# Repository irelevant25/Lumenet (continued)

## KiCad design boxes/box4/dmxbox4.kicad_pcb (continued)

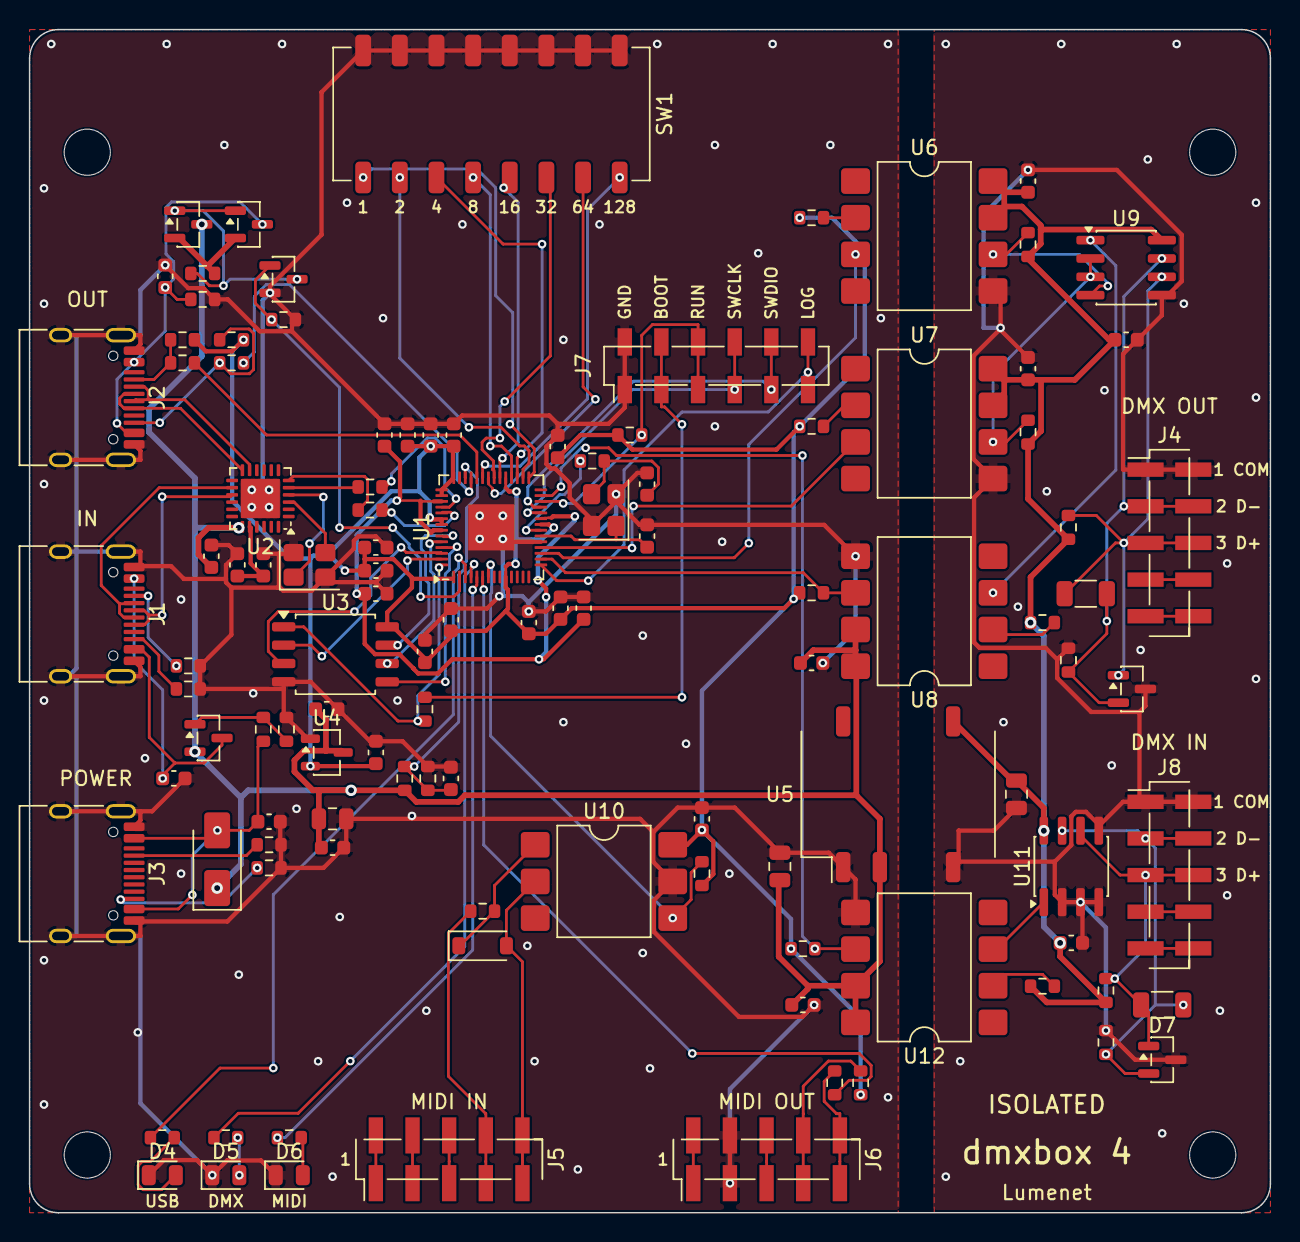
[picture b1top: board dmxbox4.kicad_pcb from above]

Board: 2 copper layers, 86.0 x 82.0 mm, 114 parts (0 on the bottom side), 84 nets.

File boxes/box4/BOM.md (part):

# dmxbox 4: parts and how to order them

dmxbox 4 (box 4) has one DMX output with RDM, one DMX input (a console plays the desk), MIDI IN and OUT, and a
USB hub: boxes can be chained, computer →
first box → second box → … over USB-C cables. Each box is its own USB network adapter on the computer.
Designators (U1, R3, …) match the [schematic](dmxbox4_schematic.pdf) and the [assembly drawing](dmxbox4_assembly.pdf).

The board is 86 × 82 mm, two layers. JLCPCB makes it and solders every part on it, all on the top side. You make
four cables to the sockets in the box wall.

## 1. The board from JLCPCB

Upload [jlcpcb/dmxbox4_gerbers.zip](jlcpcb/dmxbox4_gerbers.zip) on the PCB quote page. The defaults fit:
2 layers, FR-4, 1.6 mm, any color, HASL lead-free, 5 boards. Then switch on **PCB Assembly**:

* Economic, top side, the number of boards to assemble (2 is the minimum).
* BOM: [jlcpcb/dmxbox4_bom.csv](jlcpcb/dmxbox4_bom.csv); placement: [jlcpcb/dmxbox4_cpl.csv](jlcpcb/dmxbox4_cpl.csv).
* Check the placement preview: JLCPCB's pink pin-1 dot of every chip and transistor must sit at the pin-1 mark of
  the silkscreen, the diodes' "−" at their band, the USB sockets' openings at the board edge, J4 to J7 along their
  pads (either end first is fine) and SW1's keys towards the board edge. KiCad and JLCPCB do not agree on every
  part's rotation: the CPL file turns each part the way JLCPCB's preview of 27 November 2026 showed it right.
  Tick **Confirm Parts Placement** and JLCPCB's engineers check it too.

110 parts on 43 lines, all in stock on 28 November 2026. Eleven are extended parts (about $3 each per order):

| Ref | Part | LCSC |
|---|---|---|
| U1 | Raspberry Pi RP2040 | C2040 |
| U2 | WCH CH334F, USB 2.0 hub | C5187527 |
| Y1, Y2 | Abracon ABM8-272-T3, 12 MHz (the crystal Raspberry Pi names for the RP2040) | C20625731 |
| U9, U11 | ST ST485BDR, RS-485 (MAX485 pins, 0.3 mA): DMX OUT, DMX IN | C91197 |
| J1, J2, J3 | HRO TYPE-C-31-M-12, USB-C sockets | C165948 |
| U5 | EVISUN B0505XT-1WR3, isolated 5 V to 5 V, 1 W, 1.5 kV (Mornsun's package and pins) | C19188495 |
| U6, U7, U8, U12 | Lite-On 6N137S-TA1-L, optocoupler: DMX send, direction, receive; DMX IN | C92651 |
| U10 | Everlight H11L1S(TA), optocoupler for MIDI IN (MIDI senders at 3.3 V give too little current for a 6N137) | C78589 |
| J4, J8, J5, J6 | hanxia SMD pin header 1 × 5, 2.54 mm: DMX OUT, DMX IN, MIDI IN, MIDI OUT | C41417362 |
| J7 | hanxia SMD socket strip (female) 1 × 6, 2.54 mm: the service pins | C42380984 |
| SW1 | kangshen DSPV08LSGET, piano DIP switch with 8 keys: the box number | C3293170 |

Everything else is a basic part: W25Q128JVSIQ flash, XC6206 3.3 V regulator, AO3401A and 2N7002 transistors,
SS34, 1N4148W, PSM712 (protection of the DMX lines), LEDs, resistors and capacitors. For 5 boards: about $63 of
parts and $43 of fees, plus the boards and shipping (`scripts/check_parts.py` asks JLCPCB for today's numbers).

## 2. What you buy and fit

| Qty | For | Part | Notes |
|---|---|---|---|
| 1 | DMX OUT | XLR 5-pin **female** panel socket XLR-5G-C | In the back wall. |
| 1 | DMX IN | XLR 5-pin **male** panel socket XLR-5W-C | In the back wall, beside DMX OUT. |
| 2 | MIDI IN, MIDI OUT | REAN NYS325, DIN 5-pin 180° female | In the back wall. |
| 4 | J4, J8, J5, J6 | 5 wires with a 1 × 5 female housing, 2.54 mm (Dupont) | From the pin headers on the board to the sockets. |
| 1 | J7 | jumper wire, male to male | For BOOT and RUN, see [below](#6-the-service-pins-j7). |
| | | the printed case | See [section 4](#4-the-case): about 100 g of PETG. |
| 4 | | M3 heat-set inserts, 5.7 mm long, 4.6 mm wide (for example Ruthex M3 × 5.7) | In the case's four posts. |
| 4 | H1 to H4 | M3 hex standoffs, male-female, 25 mm | Through the board into the inserts; the lid sits on them. |
| 4 | | M3 countersunk screws, 6 mm (ISO 10642) | The lid, into the standoffs. |
| 4 | | M3 screws, 10 mm, and nuts | The two XLRs. |
| 4 | | M3 screws, 8 mm, and nuts | The two DINs. |
| 3 | D4, D5, D6 | round light pipes, 3 mm, 25.4 mm (1 inch) below their head, for a 3.2 mm hole | Pushed into the lid, over the LEDs. |
| 4 | | rubber feet | If you like. |

## 3. Wiring the sockets

Pin n of the header is the socket's pin n on all four (pin 1 is at the "1" on the board):

| Header | Socket | Pin 1 | Pin 2 | Pin 3 | Pin 4 | Pin 5 |
|---|---|---|---|---|---|---|
| J4 | DMX OUT (XLR) | common | Data − | Data + | free | free |
| J8 | DMX IN (XLR, male) | common | Data − | Data + | free | free |
| J5 | MIDI IN (DIN) | free | free (MIDI IN leaves its shield open) | free | current in | current out |
| J6 | MIDI OUT (DIN) | free | shield (ground) | free | current out | current in |

J4 and J8 are on the isolated side: pin 1 is the DMX common, not the box's ground.

## 4. The case

A base and a lid printed in PETG, 123 × 127 × 36 mm closed, wider than the board for the four sockets in a row
(seen from behind: MIDI IN, MIDI OUT, DMX IN, DMX OUT):
[case_print/dmxbox4_base.stl](case_print/dmxbox4_base.stl) and [case_print/dmxbox4_lid.stl](case_print/dmxbox4_lid.stl),
each already turned as it prints (the base standing on its floor, the lid on its top). Pictures:
[from the front](3d/dmxbox4_print_front.png), [from the back](3d/dmxbox4_print_back.png),
[opened](3d/dmxbox4_print_open.png). `scripts/make_print_case.py` makes them from the board's layout;
`case_print/dmxbox4_case_print.step` has both parts for changes in a CAD program.

Printing (Bambu Lab P1S, 0.4 mm nozzle, Bambu Studio):

* Filament: your PETG profile. Plate: textured PEI; on a smooth one, glue stick first (PETG holds too hard).
* Layer height 0.2 mm, 5 walls, 5 top and 5 bottom layers, 20 % gyroid infill. No supports and no brim: the
  round holes in the back wall have a flat top that bridges, under the sockets' flanges.
* The labels are 0.6 mm deep. For them in a second color (AMS): load `dmxbox4_base.stl` together with
  `dmxbox4_base_text.stl`, answer "Yes" to loading them as one object of several parts, and give the text part
  the other filament. The same for the lid.

The holes come out a little small when printed; they are drawn 0.1 to 0.3 mm larger. If a socket or a light
pipe is still tight, a drill or a small file by hand is enough.

The case does not conduct, so the DMX side's isolation cannot be bridged through it, and any screws will do.

The aluminium case of [section 7](#7-the-aluminium-case-instead) is the other way, with the same board.

## 5. Putting it together

1. Press the four heat-set inserts into the posts of the base: a soldering iron at about 240 °C, straight down
   until each one is flush, then let it cool.
2. Solder the four cables to the XLR and DIN sockets (pin n to pin n) and screw the sockets into the back wall,
   the nuts inside.
3. Set the board on the posts, SW1 towards the slot in the side and the USB-C sockets in the front openings.
   Screw the four standoffs through its holes into the inserts. Plug the cables onto J4, J8, J5 and J6.
4. Push the three light pipes into the lid from above, put the lid on (its lip goes inside the walls) and screw
   it to the standoffs.
5. Set the box number with SW1, through the slot with a pen tip: a key pressed down adds the number printed
   next to it (1, 2, 4 … 128; go by these, not by any numbers on the switch itself). With the number n the box
   has the address 10.1.n.1 and Art-Net universe n; every box on one computer needs its own number.
6. Plug IN into a computer. A new box has an empty flash, so the RP2040 starts its USB boot loader and a drive
   called RPI-RP2 appears. Run `firmware\build.cmd` once (see DEV.md), then `firmware\flash.cmd`: it copies the
   firmware onto it. Later updates go the same way; flash.cmd then asks the box to restart into its boot loader
   by itself.

## 6. The service pins (J7)

Normally nothing is plugged in here (the case has to come apart for it). The names are on the board, above
the pins:

| Pin | Name | What it is for |
|---|---|---|
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
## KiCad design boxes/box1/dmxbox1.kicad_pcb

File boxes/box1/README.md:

# Box 1: dmxbox 1, the box with the Pico

A Raspberry Pi Pico in socket strips, one DMX output with RDM and the box-number switch; the Pico's micro-USB is
the box's USB socket. Every part is through-hole: JLCPCB makes the bare board and you solder it. Not built yet.

| File or folder | What |
|---|---|
| [BOM.md](BOM.md) | What to order and buy, soldering, the case and putting the box together |
| `jlcpcb/` | The Gerber ZIP for JLCPCB (the board only) |
| `dmxbox1_schematic.pdf`, `dmxbox1_assembly.pdf`, `dmxbox1_copper.pdf` | The drawings |
| `case_print/` | The case printed in PETG: STL files for the slicer |
| `3d/` | The Blender model and the pictures |
| `firmware/` | `box.h` and `dmxbox1.h` make the shared RP2040 firmware box 1's; `build.cmd` builds `dmxbox1.uf2`, `flash.cmd` puts it onto a box |
| `dmxbox1.kicad_*`, `dmxbox1.pretty/` | The KiCad project, made by the scripts |
| `scripts/` | Make the board, the drawings, the pictures and the case from `circuit.py`, with the scripts all boxes share (`boxes/scripts`) |
| [perfboard/](perfboard/README.md) | The first box 1, built on a perfboard (2026-11-19): it only sends, has no switch and answers at 192.168.7.1; its firmware is in `firmware/archive/pico` |

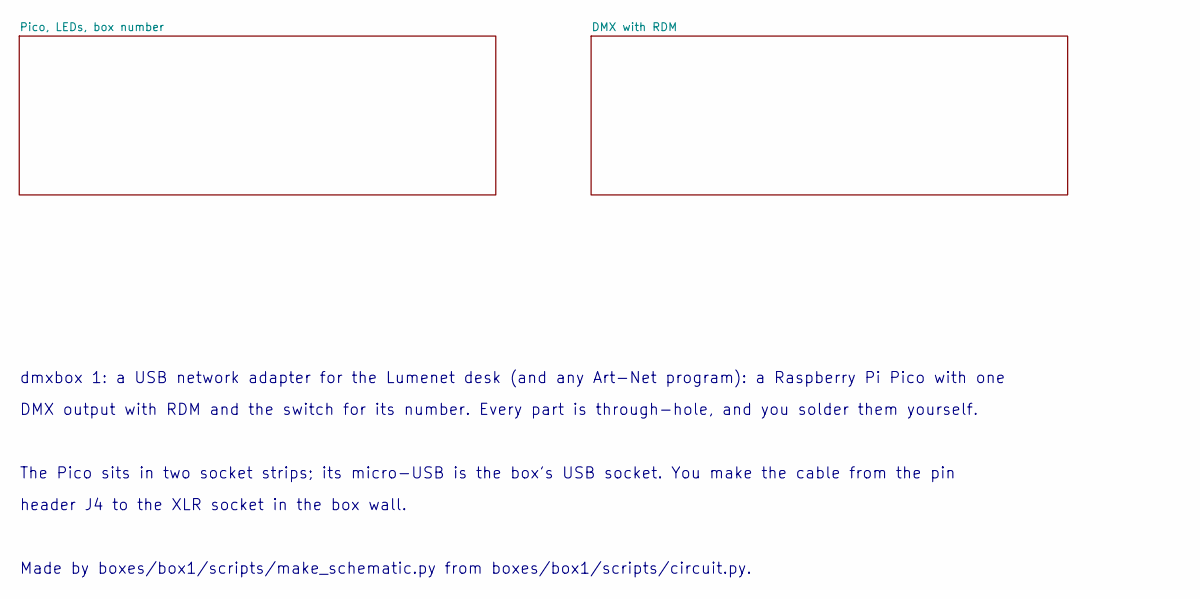
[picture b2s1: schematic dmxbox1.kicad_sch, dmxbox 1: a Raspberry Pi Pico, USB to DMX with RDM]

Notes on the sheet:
dmxbox 1: a USB network adapter for the Lumenet desk (and any Art-Net program): a Raspberry Pi Pico with one
DMX output with RDM and the switch for its number. Every part is through-hole, and you solder them yourself.
The Pico sits in two socket strips; its micro-USB is the box's USB socket. You make the cable from the pin
header J4 to the XLR socket in the box wall.
Made by boxes/box1/scripts/make_schematic.py from boxes/box1/scripts/circuit.py.

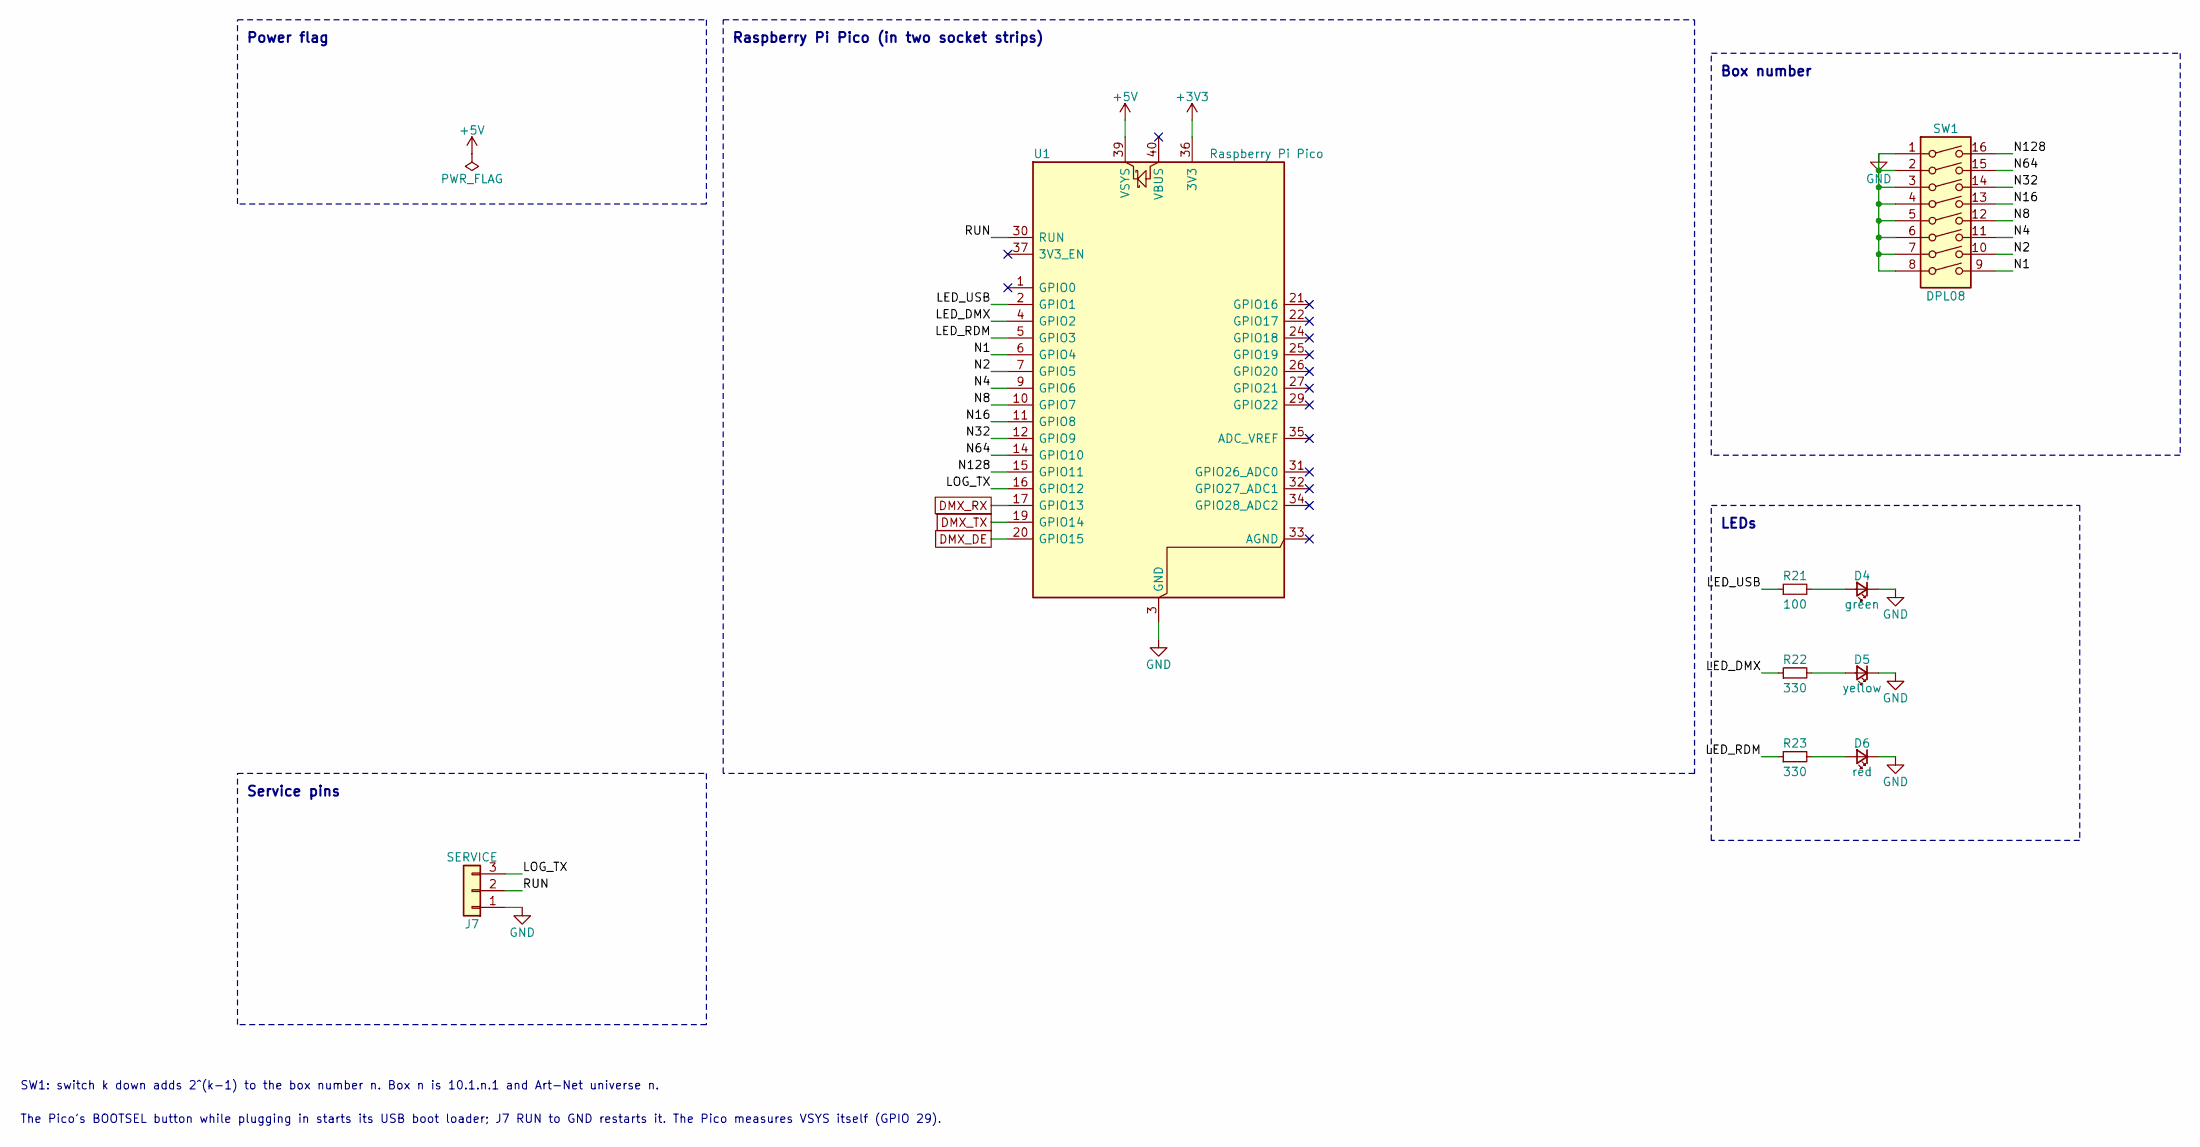
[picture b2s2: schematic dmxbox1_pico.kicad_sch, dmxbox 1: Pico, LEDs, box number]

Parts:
D4: green; LED_D3.0mm
D5: yellow; LED_D3.0mm
D6: red; LED_D3.0mm
J7: SERVICE; PinHeader_1x03_P2.54mm_Vertical
R21: 100; R_Axial_DIN0207_L6.3mm_D2.5mm_P7.62mm_Horizontal
R22, R23: 330; R_Axial_DIN0207_L6.3mm_D2.5mm_P7.62mm_Horizontal
SW1: DPL08; SW_DIP_SPSTx08_Piano_10.8x21.88mm_W7.62mm_P2.54mm
U1: Raspberry Pi Pico; RaspberryPi_Pico_Common_THT

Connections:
+3V3: U1.36 (3V3); also elsewhere on the board
+5V: U1.39 (VSYS); also elsewhere on the board
/Pico, LEDs, box number/LED_DMX: R22.1, U1.4 (GPIO2)
/Pico, LEDs, box number/LED_RDM: R23.1, U1.5 (GPIO3)
/Pico, LEDs, box number/LED_USB: R21.1, U1.2 (GPIO1)
/Pico, LEDs, box number/LOG_TX: J7.3, U1.16 (GPIO12)
/Pico, LEDs, box number/N1: SW1.9, U1.6 (GPIO4)
/Pico, LEDs, box number/N2: SW1.10, U1.7 (GPIO5)
/Pico, LEDs, box number/N4: SW1.11, U1.9 (GPIO6)
/Pico, LEDs, box number/N8: SW1.12, U1.10 (GPIO7)
/Pico, LEDs, box number/N16: SW1.13, U1.11 (GPIO8)
/Pico, LEDs, box number/N32: SW1.14, U1.12 (GPIO9)
/Pico, LEDs, box number/N64: SW1.15, U1.14 (GPIO10)
/Pico, LEDs, box number/N128: SW1.16, U1.15 (GPIO11)
/Pico, LEDs, box number/RUN: J7.2, U1.30 (RUN)
DMX_DE: U1.20 (GPIO15); also elsewhere on the board
DMX_RX: U1.17 (GPIO13); also elsewhere on the board
DMX_TX: U1.19 (GPIO14); also elsewhere on the board
GND: D4.1 (K), D5.1 (K), D6.1 (K), J7.1, SW1.1, SW1.2, SW1.3, SW1.4, SW1.5, SW1.6, SW1.7, SW1.8, U1.3 (GND), U1.8 (GND), U1.13 (GND), U1.18 (GND), U1.23 (GND), U1.28 (GND), U1.38 (GND); also elsewhere on the board
unnamed: D4.2 (A), R21.2
unnamed: D5.2 (A), R22.2
unnamed: D6.2 (A), R23.2

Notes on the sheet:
Raspberry Pi Pico (in two socket strips)
Power flag
Service pins
LEDs
Box number
SW1: switch k down adds 2^(k-1) to the box number n. Box n is 10.1.n.1 and Art-Net universe n.
The Pico's BOOTSEL button while plugging in starts its USB boot loader; J7 RUN to GND restarts it. The Pico measures VSYS itself (GPIO 29).

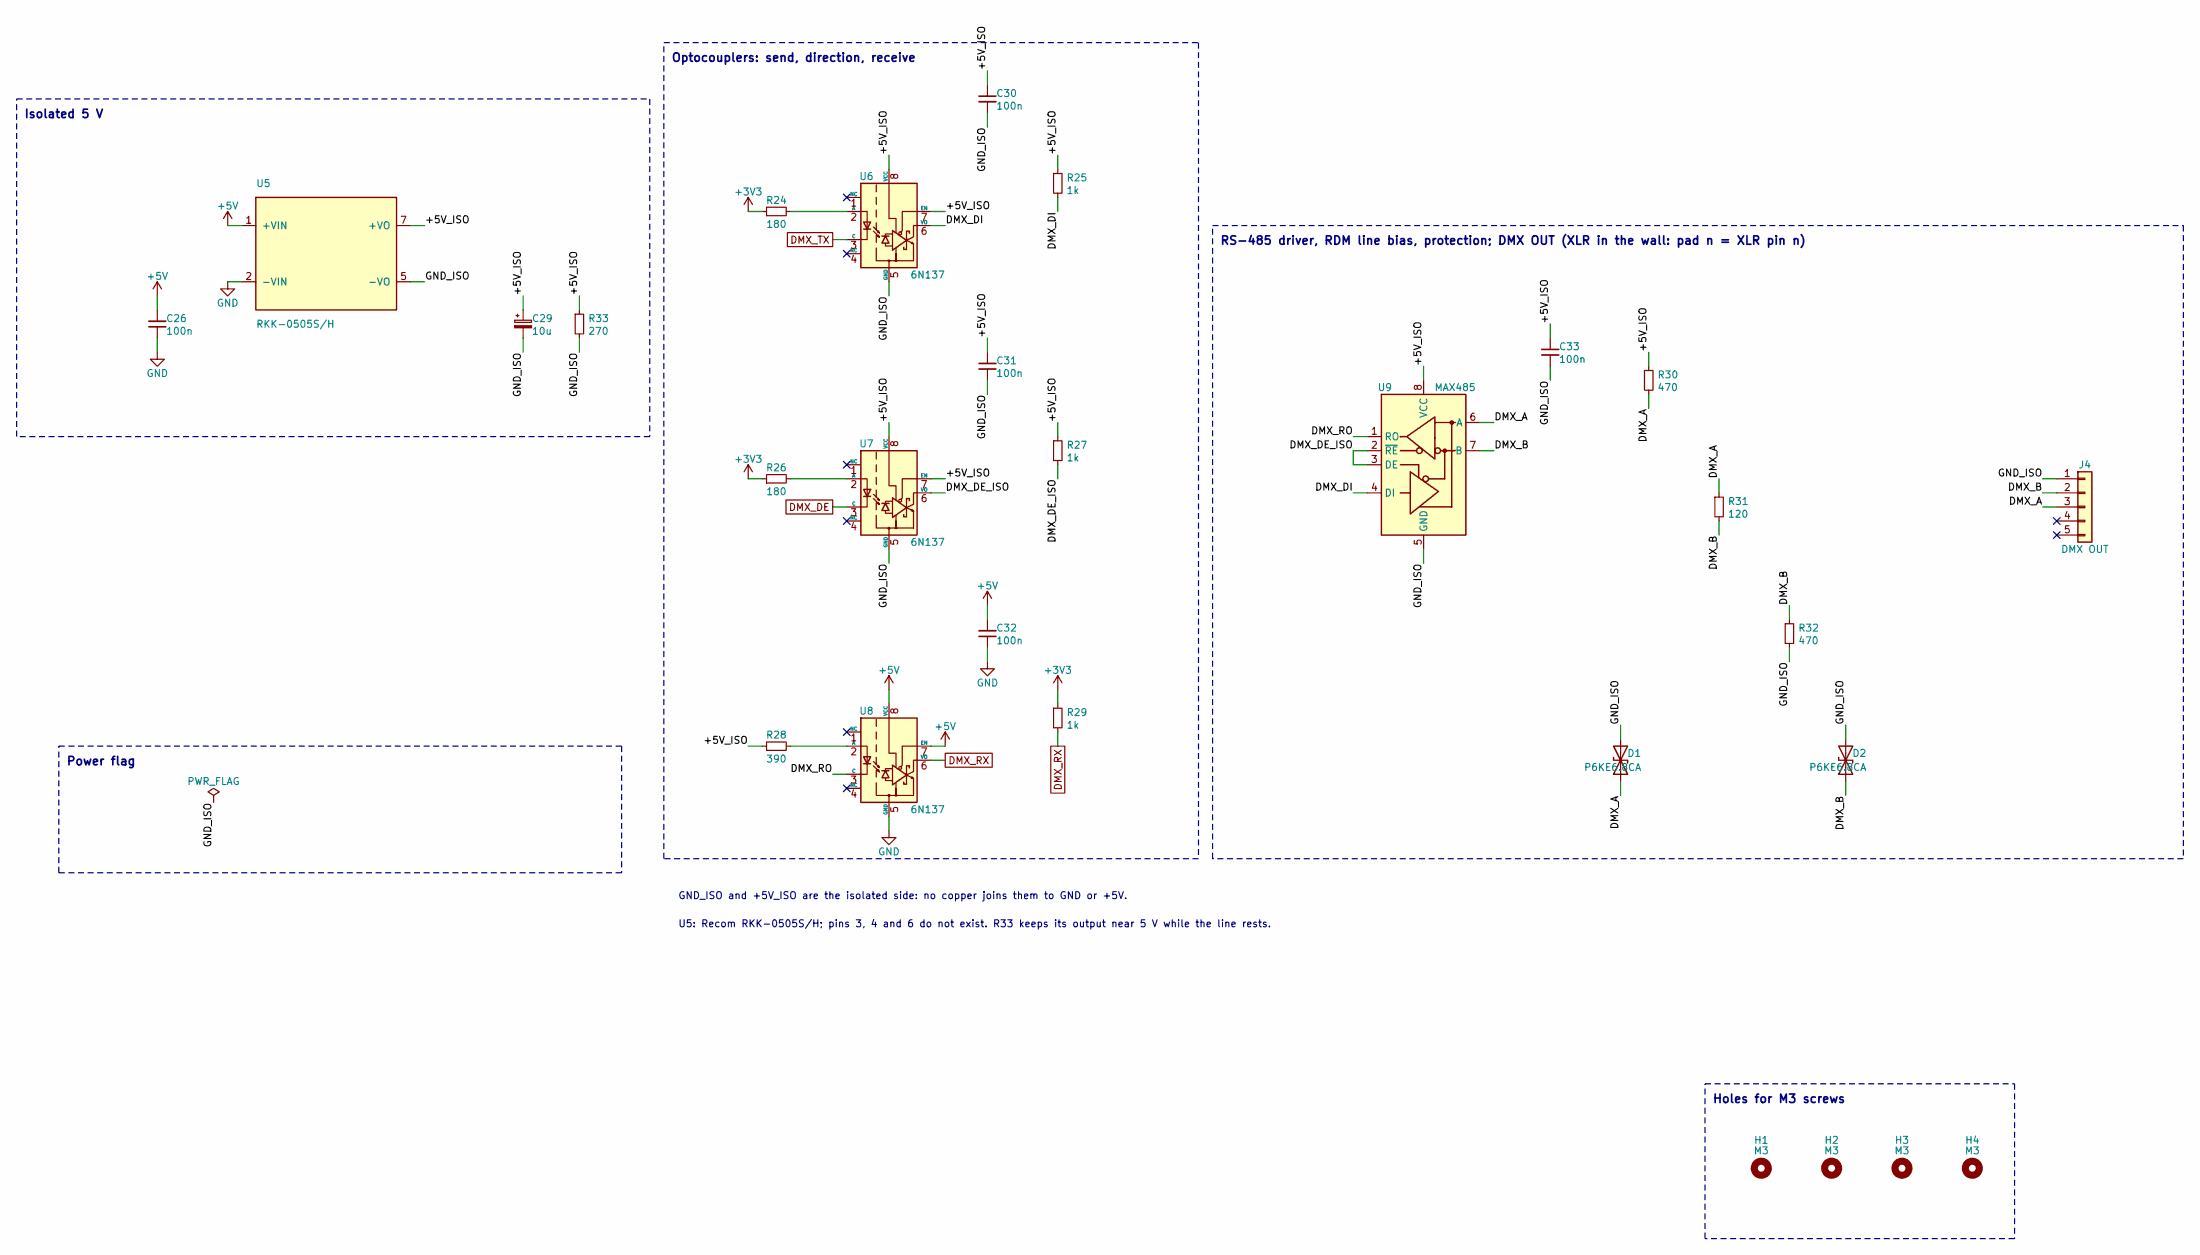
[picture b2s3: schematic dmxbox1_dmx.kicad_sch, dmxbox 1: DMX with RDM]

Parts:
C26, C30, C31, C32, C33: 100n; C_Disc_D5.0mm_W2.5mm_P5.00mm
C29: 10u; CP_Radial_D5.0mm_P2.00mm
D1, D2: P6KE6.8CA; D_DO-15_P10.16mm_Horizontal
H1, H2, H3, H4: M3; MountingHole_3.2mm_M3
J4: DMX OUT; PinHeader_1x05_P2.54mm_Vertical
R24, R26: 180; R_Axial_DIN0207_L6.3mm_D2.5mm_P7.62mm_Horizontal
R25, R27, R29: 1k; R_Axial_DIN0207_L6.3mm_D2.5mm_P7.62mm_Horizontal
R28: 390; R_Axial_DIN0207_L6.3mm_D2.5mm_P7.62mm_Horizontal
R30, R32: 470; R_Axial_DIN0207_L6.3mm_D2.5mm_P7.62mm_Horizontal
R31: 120; R_Axial_DIN0207_L6.3mm_D2.5mm_P7.62mm_Horizontal
R33: 270; R_Axial_DIN0207_L6.3mm_D2.5mm_P7.62mm_Horizontal
U5: RKK-0505S/H; Converter_DCDC_RECOM_RKK_SIP7
U6, U7, U8: 6N137; DIP-8_W7.62mm_Socket
U9: MAX485; DIP-8_W7.62mm_Socket

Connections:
+3V3: R24.1, R26.1, R29.1; also elsewhere on the board
+5V: C26.1, C32.1, U5.1 (+VIN), U8.7 (EN), U8.8 (VCC); also elsewhere on the board
/DMX with RDM/+5V_ISO: C29.1, C30.1, C31.1, C33.1, R25.1, R27.1, R28.1, R30.1, R33.1, U5.7 (+VO), U6.7 (EN), U6.8 (VCC), U7.7 (EN), U7.8 (VCC), U9.8 (VCC)
/DMX with RDM/DMX_A: D1.1 (A1), J4.3, R30.2, R31.1, U9.6 (A)
/DMX with RDM/DMX_B: D2.1 (A1), J4.2, R31.2, R32.1, U9.7 (B)
/DMX with RDM/DMX_DE_ISO: R27.2, U7.6 (VO), U9.2 (~RE), U9.3 (DE)
/DMX with RDM/DMX_DI: R25.2, U6.6 (VO), U9.4 (DI)
/DMX with RDM/DMX_RO: U8.3 (C), U9.1 (RO)
/DMX with RDM/GND_ISO: C29.2, C30.2, C31.2, C33.2, D1.2 (A2), D2.2 (A2), J4.1, R32.2, R33.2, U5.5 (-VO), U6.5 (GND), U7.5 (GND), U9.5 (GND)
DMX_DE: U7.3 (C); also elsewhere on the board
DMX_RX: R29.2, U8.6 (VO); also elsewhere on the board
DMX_TX: U6.3 (C); also elsewhere on the board
GND: C26.2, C32.2, U5.2 (-VIN), U8.5 (GND); also elsewhere on the board
unnamed: R24.2, U6.2 (A)
unnamed: R26.2, U7.2 (A)
unnamed: R28.2, U8.2 (A)

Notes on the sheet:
Isolated 5 V
Optocouplers: send, direction, receive
RS-485 driver, RDM line bias, protection; DMX OUT (XLR in the wall: pad n = XLR pin n)
Holes for M3 screws
Power flag
GND_ISO and +5V_ISO are the isolated side: no copper joins them to GND or +5V.
U5: Recom RKK-0505S/H; pins 3, 4 and 6 do not exist. R33 keeps its output near 5 V while the line rests.

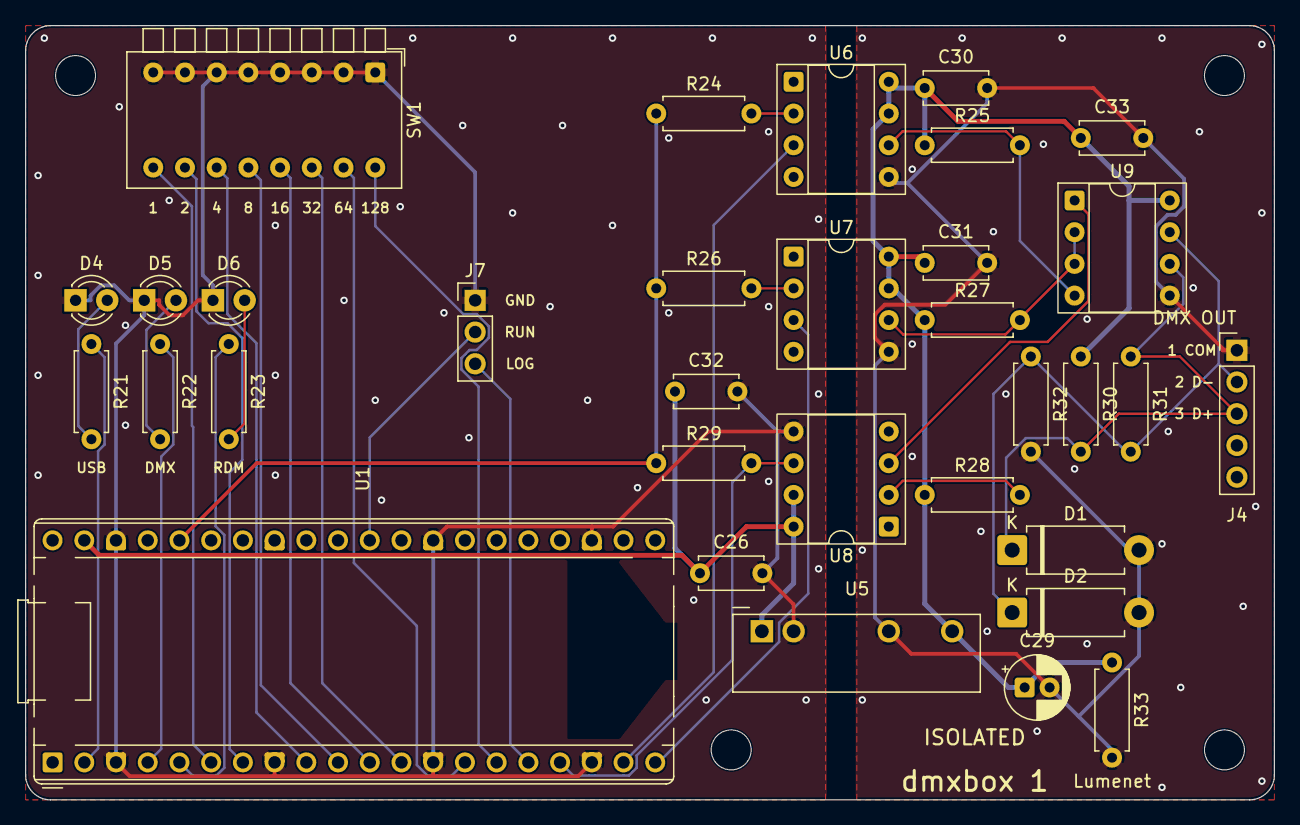
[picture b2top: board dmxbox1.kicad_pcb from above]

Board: 2 copper layers, 100.0 x 62.0 mm, 37 parts (0 on the bottom side), 32 nets.

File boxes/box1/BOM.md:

# dmxbox 1: parts and how to build it

dmxbox 1 (box 1) is a Raspberry Pi Pico with one DMX output with RDM and the switch for its number. The Pico's own
micro-USB is the box's USB socket. Every part is through-hole: JLCPCB makes the bare board and you solder the parts.
Designators (U1, R24, …) match the [schematic](dmxbox1_schematic.pdf) and the
[assembly drawing](dmxbox1_assembly.pdf); the parts that do what box 4's do have box 4's names, so there are gaps.

The board is 100 × 62 mm, two layers.

## 1. The board from JLCPCB

Upload [jlcpcb/dmxbox1_gerbers.zip](jlcpcb/dmxbox1_gerbers.zip) on the PCB quote page. The defaults fit: 2 layers,
FR-4, 1.6 mm, any color, HASL lead-free, 5 boards. No assembly: you solder the parts.

## 2. What you buy

| Qty | Ref | Part | Notes |
|---|---|---|---|
| 1 | U1 | Raspberry Pi Pico | The plain Pico, or the Pico H (its headers already on). |
| 2 | U1 | pin header, male, 1 × 20, 2.54 mm | Only for a plain Pico: solder them to it, pins down. |
| 2 | U1 | socket strip, female, 1 × 20, 2.54 mm, 8.5 mm high | On the board; the Pico plugs in. |
| 3 | U6, U7, U8 | 6N137, optocoupler, DIP-8 | |
| 1 | U9 | MAX485 or SN75176BP, RS-485, DIP-8 | The same pins. |
| 4 | U6 to U9 | IC socket DIP-8, 7.62 mm | |
| 1 | U5 | Recom RKK-0505S/H, isolated DC-DC 5 V to 5 V, 1 W | SIP7 with 4 pins: it fits one way only. |
| 1 | SW1 | piano DIP switch, 8 keys, through-hole, rows 7.62 mm apart (for example ONPOW DPL08RGT) | The keys at the board edge. |
| 1 each | D4, D5, D6 | LED 3 mm: green, yellow, red | |
| 2 | D1, D2 | P6KE6.8CA, TVS diode, DO-15 | "CA": both ways, so either way round. |
| 1 | R21 | 100 Ω | Resistors: 0.25 W, axial (0207), legs bent to 7.62 mm. |
| 2 | R22, R23 | 330 Ω | |
| 2 | R24, R26 | 180 Ω | |
| 3 | R25, R27, R29 | 1 kΩ | |
| 1 | R28 | 390 Ω | |
| 2 | R30, R32 | 470 Ω | |
| 1 | R31 | 120 Ω | |
| 1 | R33 | 270 Ω | |
| 5 | C26, C30 to C33 | 100 nF, ceramic, 5 mm lead spacing | |
| 1 | C29 | 10 µF, electrolytic, 16 V or more, 5 mm wide, 2 mm lead spacing | Mind its "−" stripe. |
| 1 | J4 | pin header, male, 1 × 5, 2.54 mm | To the XLR socket. |
| 1 | J7 | pin header, male, 1 × 3, 2.54 mm | The service pins: GND, RUN, LOG. |
| 1 | DMX OUT | XLR 5-pin **female** panel socket XLR-5G-C | In the back wall. |
| 1 | J4 | 5 wires with a 1 × 5 female housing, 2.54 mm (Dupont) | From J4 to the XLR socket. |
| | | the printed case | See [section 4](#4-the-case): about 70 g of PETG. |
| 4 | | M3 heat-set inserts, 5.7 mm long, 4.6 mm wide (for example Ruthex M3 × 5.7) | In the case's four posts. |
| 4 | H1 to H4 | M3 hex standoffs, male-female, 25 mm | Through the board into the inserts; the lid sits on them. |
| 4 | | M3 countersunk screws, 6 mm (ISO 10642) | The lid, into the standoffs. |
| 2 | | M3 screws, 10 mm, and nuts | The XLR. |
| 3 | D4, D5, D6 | round light pipes, 3 mm, about 19 mm below their head, for a 3.2 mm hole | The LEDs stand 8.3 mm high: a 25.4 mm pipe cut to 19 mm. |
| 4 | | rubber feet | If you like. |
| 1 | | micro-USB cable, for data (not charge-only) | |

## 3. Soldering

Low parts first, so the board lies flat while you solder: the resistors, the diodes D1 and D2, the ceramic
capacitors, the four IC sockets (their notch as on the board), the two socket strips of the Pico, J7 and J4, the
LEDs (the flat side of the rim, the cathode, as on the board; their tops about 8 mm above the board, where the
light pipes end), SW1 (its keys at the board edge), U5 (its pin 1 at the square pad) and C29 (its stripe away from the "+" on the board). Then the chips
into their sockets: the three 6N137 and the MAX485, each with its notch to the notch of the socket.

Test before the chips go in: with the Pico in its sockets and USB plugged in, about 5 V between U5's pins 7 and 5
(the isolated side: 4.6 to 5.5 V).

Wiring the XLR socket: pin n of J4 is the socket's pin n (pin 1 is "1 COM" on the board): 1 common, 2 Data −,
3 Data +, 4 and 5 free. J4 is on the isolated side: pin 1 is the DMX common, not the box's ground.

## 4. The case

A base and a lid printed in PETG, 70 × 141 × 36 mm closed: box 4's case made for this board, with the Pico's
micro-USB in the front wall and the XLR in the middle of the back wall.
[case_print/dmxbox1_base.stl](case_print/dmxbox1_base.stl) and [case_print/dmxbox1_lid.stl](case_print/dmxbox1_lid.stl),
each already turned as it prints. Pictures: [from the front](3d/dmxbox1_print_front.png),
[from the back](3d/dmxbox1_print_back.png), [opened](3d/dmxbox1_print_open.png). Print it as box 4's case
([box 4's BOM.md](../box4/BOM.md#4-the-case)).

## 5. Putting it together

1. Press the four heat-set inserts into the posts of the base: a soldering iron at about 240 °C, straight down
   until each one is flush, then let it cool.
2. Solder the cable to the XLR socket (pin n to pin n) and screw the socket into the back wall, the nuts inside.
3. Set the board on the posts, SW1 towards the slot in the side and the Pico's micro-USB in the front opening.
   Screw the four standoffs through its holes into the inserts. Plug the cable onto J4.
4. Push the three light pipes into the lid from above, put the lid on and screw it to the standoffs.
5. Set the box number with SW1, through the slot with a pen tip: a key pressed down adds the number printed
   next to it (1, 2, 4 … 128 from the left; go by these, not by any numbers on the switch itself). With the
   number n the box has the address 10.1.n.1 and Art-Net universe n; every box on one computer needs its own
   number.
6. Plug it into a computer. A new Pico has an empty flash, so it starts its USB boot loader and a drive called
   RPI-RP2 appears (otherwise hold the Pico's BOOTSEL button while plugging it in). Run `firmware\build.cmd`
   once (see DEV.md), then `firmware\flash.cmd`: it copies the firmware onto it. Later updates go the same way;
   flash.cmd then asks the box to restart into its boot loader by itself.

## 6. The service pins (J7)

| Pin | Name | What it is for |
|---|---|---|
| 1 | GND | ground, for the pins next to it |
| 2 | RUN | joined to GND for a moment: the box restarts |
| 3 | LOG | what the firmware reports, as text: to the RX of a 3.3 V USB-serial adapter (its GND to pin 1), 250000 baud |

The USB boot loader: the Pico's BOOTSEL button while you plug it in.

## Power

The box asks the computer for 250 mA and draws about 150 mA; any USB port gives that.

## The box on its perfboard

The first box 1, on a perfboard, is in [perfboard/](perfboard/README.md): it only sends (no RDM) and has no switch,
answers at 192.168.7.1 and keeps its first firmware (`firmware/archive/pico`); the desk plays it as before.

## Not built yet

This board is the first revision: nothing of it has been built or measured. It passes KiCad's electrical and
design rule checks, and its nets match the schematic.

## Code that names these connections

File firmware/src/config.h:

// dmxbox 3 (RP2040: one DMX output with RDM, MIDI in and out, a USB hub for a
// chain of boxes) - build-time configuration. Everything you are likely to
// change lives here. This file holds numbers only, so the simulator
// (firmware/sim) and the tests (firmware/test) use it too.
#pragma once

#define FW_VERSION_MAJOR 3
#define FW_VERSION_MINOR 0

// ---------------------------------------------------------------- network (inside the USB cable)
// The box shows up on the computer as a USB network adapter and hands the
// computer its address by itself (a tiny DHCP server).
//
// The address comes from the switch SW1 on the board. Its eight switches give
// the box number n, 0 to 255 (switch 1 counts 1, switch 2 counts 2, switch 3
// counts 4 ... switch 8 counts 128; ON counts). The box is 10.1.n.1 and the
// computer gets 10.1.n.2, so every box is a small network of its own, and
// several boxes can be plugged into one computer, also one behind the other.
// Give every box its own number. Lumenet looks for 10.1.n.1 on every network
// adapter of the computer that has an address 10.1.n.x.
//
// If a network you use is in 10.1.x.x, change the first two numbers here.
#define NET_FIRST     10                     // the first two numbers of both addresses
#define NET_SECOND    1
#define NET_NETMASK   {255, 255, 255, 0}
#define NET_LEASE_S   3600                   // the computer asks again after at most this many seconds
// Both Ethernet addresses are made from the box number too: box
// 02:00:0A:01:nn:01, computer 02:00:0A:01:nn:02.

#define ARTNET_PORT    6454   // fixed by the Art-Net spec
#define CTRL_PORT      7000   // our own reliable command protocol
// Art-Net: box n listens to universe ARTNET_UNIVERSE + n.
#define ARTNET_UNIVERSE   0
#define NODE_SHORT_NAME "dmxbox 3"
#define NODE_LONG_NAME  "dmxbox 3 - RP2040 USB Art-Net node with RDM and MIDI"

// In MERGE_ARTNET_OVERRIDE mode, Art-Net is "live" for this long after the
// last packet. After that the box falls back to the cue layer.
#define ARTNET_LIVE_MS 3000

// ---------------------------------------------------------------- USB identity
// 0x1209 / 0x0001 is the "for testing only" number pair of pid.codes. It is
// fine for a private prototype; a box that is given away or sold needs its own
// pair. The USB serial number is "box-" and the box number ("box-007").
#define USB_VID          0x1209
#define USB_PID          0x0001
#define USB_MANUFACTURER "dmxbox"
#define USB_PRODUCT      "dmxbox 3"
// The box sits behind the hub chip on its own board. A hub port may give a
// device 100 mA when the hub takes its own power from the cable; asking for
// more, the computer would refuse the box. What the board really draws (hub,
// RP2040, DMX side: about 200 mA) is the hub's business, see BOM.md.
#define USB_MAX_POWER_MA 100

// ---------------------------------------------------------------- DMX
#ifndef DMX_OUTPUTS
#define DMX_OUTPUTS  1          // one DMX socket. The simulator also builds a box with two (for tests).
#endif
#define DMX_CHANNELS (512 * DMX_OUTPUTS)   // 512 for each: Lumenet counts the outputs from it
// Break 193 us, mark after break 17 us: see dmx_tx.pio.

// ---------------------------------------------------------------- RDM
// The box's own RDM ID: manufacturer 7FF0 (E1.20 keeps 7FF0 to 7FFF for
// prototypes), then four bytes of the flash chip's serial number.
#define RDM_MANUFACTURER 0x7FF0

// ---------------------------------------------------------------- presets
#define PRESET_SLOTS 16         // 16 x 512 bytes, in the last 12 KB of the flash

// ---------------------------------------------------------------- pins
// GPIO numbers of the RP2040; hardware/scripts/circuit.py has the same list.
#define PIN_OUT_EN    0         // high = 5 V on the OUT socket, for the next box
#define PIN_LED_USB   1         // green: a computer uses the box
#define PIN_LED_DMX   2         // yellow: DMX goes out, flickers with lighting data
#define PIN_LED_MIDI  3         // red: MIDI and RDM traffic
#define PIN_MIDI_TX   4         // UART1, 31250 baud
#define PIN_MIDI_RX   5
#define PIN_LOG_TX    12        // UART0 TX: the log, 250000 baud, on the service pads J7 (pin 6)
#define PIN_DMX_RX    13        // UART0 RX: RDM answers, 250000 baud
#define PIN_DMX_TX    14        // PIO: DMX and RDM out. Low = optocoupler LED on = line low.
#define PIN_DMX_DE    15        // low = listen (RDM), high = send; the line sends while the RP2040 is off
#define PIN_BOX_N1    18        // SW1 switch 1 to 8: GPIO 18 to 25, ON = low
#define PIN_CC1       26        // ADC0: CC1 of the OUT socket
#define PIN_CC2       27        // ADC1: CC2 of the OUT socket
#define PIN_VSENSE    28        // ADC2: half the supply voltage

#define LOG_BAUD      250000    // the log shares UART0 with the RDM answers, so it has their speed
